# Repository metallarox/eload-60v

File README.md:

# eload-60v — 4-channel electronic load, 60 V · 20 A · 300 W

An open-hardware DC electronic load with four independent constant-current channels, 20-bit measurement on every channel, a hardware fail-safe that does not depend on firmware, and WiFi control through a plug-in ESP8266 module.

> **Status: rev 0.3 — design complete, not yet built or bench-tested.**
> ERC and DRC (with schematic parity) are clean, and the control loop and thermal budget have been analysed numerically. Treat it as a reviewed design, not a proven product. Bench reports, issues and pull requests are very welcome.

## Specifications

| Parameter | Value |
|---|---|
| Input voltage | 0 – 60 V (hardware OVP trips at 64.7 V) |
| Current | 4 channels × 0 – 5 A = 20 A |
| Power | 4 × 75 W = 300 W continuous (power-limited above 15 V) |
| Mode | Constant current per channel; CP / CR in firmware |
| Setpoint | DAC8565, 16 bit → 76 µA per LSB per channel |
| Measurement | INA228 per channel: 20-bit, Kelvin shunt, remote voltage sense |
| Control | WiFi, Wemos LOLIN D1 mini Pro (ESP8266) on sockets; front panel with I²C OLED, encoder and OUTPUT button |
| Protection | OVP, OTP, per-channel over-current/over-power ALERT, reverse-polarity crowbar, 25 A fuse |
| Loop | Phase margin ≈ 80°, closed-loop bandwidth 6 – 15 kHz (model) |
| PCB | 170 × 125 mm, 2 layers, 2 oz copper, KiCad 10 |

## How it works

- **Power path.** DUT+ → 25 A ATO fuse → VLOAD bus. A D²PAK Schottky (VS-30CTQ100S) acts as a reverse-polarity crowbar that blows the fuse, and an SMCJ64CA TVS clamps transients.
- **Channels.** Each channel is an OPA2196 integrator driving an IXYS **IXTH75N10L2** *Linear L2* MOSFET (extended FBSOA, designed for linear operation) with a 20 mΩ 4-terminal shunt (Vishay WSK2512). The setpoint is the DAC output divided by 25, referenced to the shunt's cold Kelvin pad: **I = V_DAC × 2 A/V**.
- **Measurement.** One INA228 per channel reads the shunt (Kelvin) and the remote-sense voltage. Its ALERT pin is wired to the common ARM line, so a programmed over-current or over-power limit shuts the load down in hardware.
- **Fail-safe.** ARM is active-high with a pull-down. It can be pulled low by the MCU, by the LM393 OVP/OTP comparators or by any INA228 ALERT. ARM low drives CLAMP high, which shorts all four setpoints to ground. No MCU, a reset or a boot glitch all leave the load off.
- **Thermal.** The four TO-247 parts are mounted *under* the PCB on an 80 × 70 × 6 mm copper spreader. The spreader sits at VLOAD (drain) potential, so it is isolated from an SP3/TR4-class CPU cooler by a thermal pad. Two NTC thermistors sit on the spreader.
- **Front panel (rev 0.3).** A 10-pin IDC connector carries the I²C bus to a 128 × 64 OLED (0x3C) and the encoder, its push switch, the OUTPUT button and its LED to a PCF8574 expander (0x20) on the main board. The expander's INT goes to GPIO0. The encoder works as a vernier: push toggles coarse/fine, long-press selects the channel. OUTPUT ON is the only way to arm the load from the panel.
- **Supplies.** An isolated 12 V adaptor feeds the op-amps and the fan. A 78L05 supplies the analog 5 V (DAC, comparators). A separate AP63205 buck feeds only the WiFi module, and its 3.3 V regulator powers the logic.

The full walkthrough, including SOA, thermal budget and loop-stability analysis, is in **[docs/Electronic_Load_Circuit_Walkthrough.pdf](docs/Electronic_Load_Circuit_Walkthrough.pdf)** (20 slides).

## Analysis highlights

| SOA | Loop gain |
|---|---|
|  |  |

- **SOA.** The worst steady point is 60 V × 1.25 A = 75 W per MOSFET. The guaranteed FBSOA (240 W at 80 V, T<sub>C</sub> 75 °C), derated to T<sub>C</sub> ≈ 96 °C, gives ≈ 173 W, a **2.3× margin**.
- **Thermal.** T<sub>J</sub> ≈ 119 °C at 35 °C ambient with a 0.12 K/W cooler. At the OTP trip point (spreader ~100 °C) T<sub>J</sub> ≈ 139 °C. To run 300 W continuously the cooler plus pad must be ≤ 0.22 K/W.
- **Loop.** Rev 0.1 used 10 nF compensation: stable, but only 0.6 – 1.5 kHz bandwidth and a turn-on delay of about 2 ms. **Rev 0.2 uses C6 = 1 nF and C5 = 10 nF:** PM ≈ 80°, 6 – 15 kHz, about 28 µs for small steps. A 10 mA keep-alive in firmware cuts the turn-on from the clamp to about 39 µs.

The model and scripts are in [`analysis/`](analysis/). Op-amp second pole and output resistance, the cooler's thermal resistance and the pad are **assumptions**, listed in the slides.

## Repository layout

```
hardware/
  kicad/          KiCad 10 project (eload_4ch.kicad_pro), custom symbols, DRC rules
  fabrication/    Gerbers + drill (zip) and pick-and-place positions, rev 0.3
  bom/            BOM from KiCad (CSV) and priced BOM with sources (XLSX)
docs/
  Electronic_Load_Circuit_Walkthrough.pdf   slide deck (English)
  assembly/       interactive HTML BOM, top/bottom assembly drawings
  eload_4ch_schematic.pdf, eload_4ch_pcb.pdf
  images/, reports/ (ERC / DRC)
firmware/         ESP8266 firmware (Arduino core), web page, unit tests, mock server, prebuilt bin
analysis/         loop model (sympy/scipy), large-signal sim, SOA/thermal plots
tools/generator/  Python scripts that generated the schematic and placed/routed the PCB
```

Schematic, PCB and the KiCad BOM are in English. The priced BOM workbook (`eload_4ch_bom_priced.xlsx`) and the code comments in `tools/` are still in Italian.

## Building one

1. **PCB.** Use `hardware/fabrication/eload_4ch_gerbers_rev0.3.zip`: 2 layers, 1.6 mm, **2 oz** copper. Many fabs require ≥ 0.2 mm spacing with 2 oz copper, while the INA228 MSOP-10 pads are 0.15 mm apart (the project has a local DRC exception for them). Confirm with your fab, or order 1 oz outer layers.
2. **Parts.** See `hardware/bom/eload_4ch_bom_priced.xlsx`. The electronics cost is about €126 per board at single quantities (October 2026). The four IXTH75N10L2 are about half of that and can have long factory lead times.
3. **Mechanics and front panel.** Copper spreader, insulating thermal pad (≥ 100 V), CPU cooler with a 4-wire PWM fan, M3 nylon standoffs, M5 bolts for the DUT studs. Front panel: 2.42″ SSD1309 or 1.3″ SH1106 I²C OLED, EC11 encoder with push, OUTPUT button with LED, 10-wire ribbon (≤ 20 cm). J6 pinout: 1 3V3 · 2 GND · 3 SDA · 4 GND · 5 SCL · 6 ENC_A · 7 ENC_B · 8 ENC_SW · 9 OUTPUT · 10 LED (cathode, 470 Ω on board).
4. **Assembly.** Open `docs/assembly/eload_4ch_ibom.html` in a browser: an interactive BOM that highlights where each part goes, with checkboxes to track sourced and placed parts. `docs/assembly/assembly_top.pdf` and `assembly_bottom.pdf` (the four MOSFETs) show every reference inside its part outline. The silkscreen has no overlaps: each reference designator is next to its component.
5. **Firmware.** See [firmware/README.md](firmware/README.md). A prebuilt image is in `firmware/bin/`. On first start the load opens a WiFi access point for setup; afterwards the page is at `http://eload.local`.

| Pin | GPIO | Function |
|---|---|---|
| D1 / D2 | 5 / 4 | I²C SCL / SDA → INA228 0x40 – 0x43, PCF8574 0x20, OLED 0x3C |
| D5 / D7 / D8 | 14 / 13 / 15 | SPI SCK / MOSI / SYNC → DAC8565 |
| D6 | 12 | ARM_DRV (quiet at boot) — re-assigned as output after `SPI.begin()` |
| D0 | 16 | ARM_FB read-back (100 k) |
| D3 | 0 | PCF8574 INT (front panel) |
| D4 | 2 | Fan PWM |
| RX | 3 | Fan tach |
| A0 | — | NTC1 |

## Firmware

v0.2.0 for the D1 mini Pro. It compiles and its control math is unit-tested, but it has **not yet run on hardware**.
- **Control:** CC / CP / CR with the setpoint shared by the channels, hardware and firmware protections with the trip cause reported, battery cutoff, auto-trim.
- **Pulsed load:** the sink switches between the setpoint and 10 mA at 0.1 Hz – 1 kHz with an adjustable duty, set from the panel menu or the web page.
- **Front panel:** OLED with the logo at boot, encoder used as a vernier and to drive the menu, OUTPUT button.
- **Logging:** CSV on the 14 MB flash.
- **Web:** live chart, controls, OTA update.

## ⚠️ Safety

- The whole controller, including the Wemos USB port, is referenced to **DUT−**. **USB is not isolated:** only program the module with the DUT disconnected, then update over the air. The 12 V adaptor must be isolated.
- The copper spreader and the MOSFET tabs are **live at the DUT voltage**.
- 300 W of heat is real. Do not run full power without the cooler and fan, and verify the OTP before trusting it.

## To verify on the bench

- Loop step response (1.0 ↔ 1.2 A) into a stiff supply, then with 1 m of DUT cable.
- D1 crowbar surviving the fuse I²t on reversed connection.
- Thermal resistance of the actual cooler and pad; OTP trip point.
- WiFi range with the antenna overhanging the board edge inside the enclosure.
- I²C signal integrity with the OLED on a 20 cm ribbon (2.2 kΩ pull-ups).

## Changelog

- **firmware 0.2.0** — pulsed load (frequency 0.1 Hz – 1 kHz, duty 1 – 99 %, phases ≥ 100 µs) in the panel menu, the web page, the API and the CSV.
- **firmware 0.1.0** — first firmware: control, protections, OLED + encoder panel, CSV logging, web interface, OTA.

- **rev 0.3** — front panel: PCF8574 expander, 10-pin IDC connector, debounce, I²C pull-ups 2.2 kΩ. Schematic and PCB translated to English (sheets: input, channels, control, power). Silkscreen cleaned up: no overlaps, references next to their parts; interactive BOM and assembly drawings.
- **rev 0.2** — loop compensation C6 = 1 nF, setpoint filter C5 = 10 nF (10× bandwidth, PM ≈ 80°); WiFi control with D1 mini Pro replaces STM32 + isolated USB.

## Credits

Inspired by [shufps/eload2](https://github.com/shufps/eload2). Designed by IV3HGA.

## License

- Hardware (everything under `hardware/` and `docs/`): **CERN-OHL-S-2.0** — see [LICENSE](LICENSE).
- Software (`firmware/`, `analysis/`, `tools/`): **MIT** — see [LICENSE-MIT](LICENSE-MIT).

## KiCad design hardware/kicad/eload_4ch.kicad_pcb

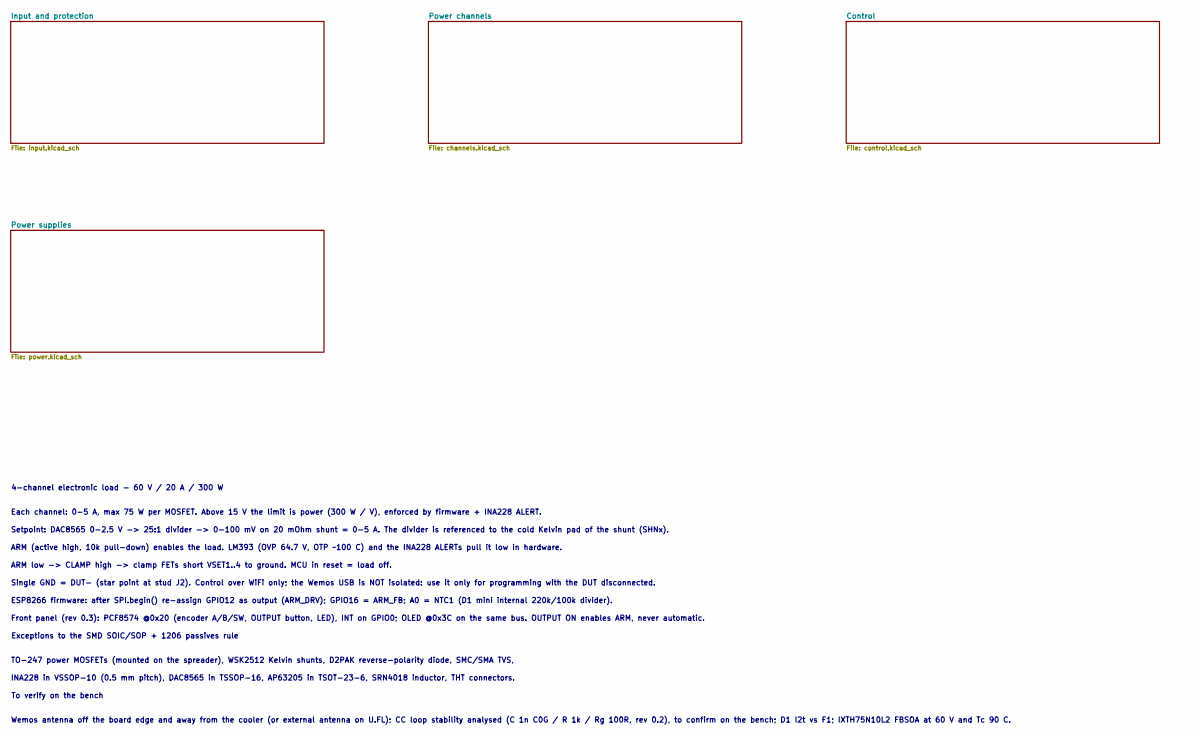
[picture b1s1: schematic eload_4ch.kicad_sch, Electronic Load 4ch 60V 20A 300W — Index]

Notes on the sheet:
Wemos antenna off the board edge and away from the cooler (or external antenna on U.FL); CC loop stability analysed (C 1n C0G / R 1k / Rg 100R, rev 0.2), to confirm on the bench; D1 I2t vs F1; IXTH75N10L2 FBSOA at 60 V and Tc 90 C.
INA228 in VSSOP-10 (0.5 mm pitch), DAC8565 in TSSOP-16, AP63205 in TSOT-23-6, SRN4018 inductor, THT connectors.
ARM low -> CLAMP high -> clamp FETs short VSET1..4 to ground. MCU in reset = load off.
Front panel (rev 0.3): PCF8574 @0x20 (encoder A/B/SW, OUTPUT button, LED), INT on GPIO0; OLED @0x3C on the same bus. OUTPUT ON enables ARM, never automatic.
Setpoint: DAC8565 0-2.5 V -> 25:1 divider -> 0-100 mV on 20 mOhm shunt = 0-5 A. The divider is referenced to the cold Kelvin pad of the shunt (SHNx).
4-channel electronic load - 60 V / 20 A / 300 W
To verify on the bench
ESP8266 firmware: after SPI.begin() re-assign GPIO12 as output (ARM_DRV); GPIO16 = ARM_FB; A0 = NTC1 (D1 mini internal 220k/100k divider).
Single GND = DUT- (star point at stud J2). Control over WiFi only; the Wemos USB is NOT isolated: use it only for programming with the DUT disconnected.
ARM (active high, 10k pull-down) enables the load. LM393 (OVP 64.7 V, OTP ~100 C) and the INA228 ALERTs pull it low in hardware.
Each channel: 0-5 A, max 75 W per MOSFET. Above 15 V the limit is power (300 W / V), enforced by firmware + INA228 ALERT.
Exceptions to the SMD SOIC/SOP + 1206 passives rule
TO-247 power MOSFETs (mounted on the spreader), WSK2512 Kelvin shunts, D2PAK reverse-polarity diode, SMC/SMA TVS,

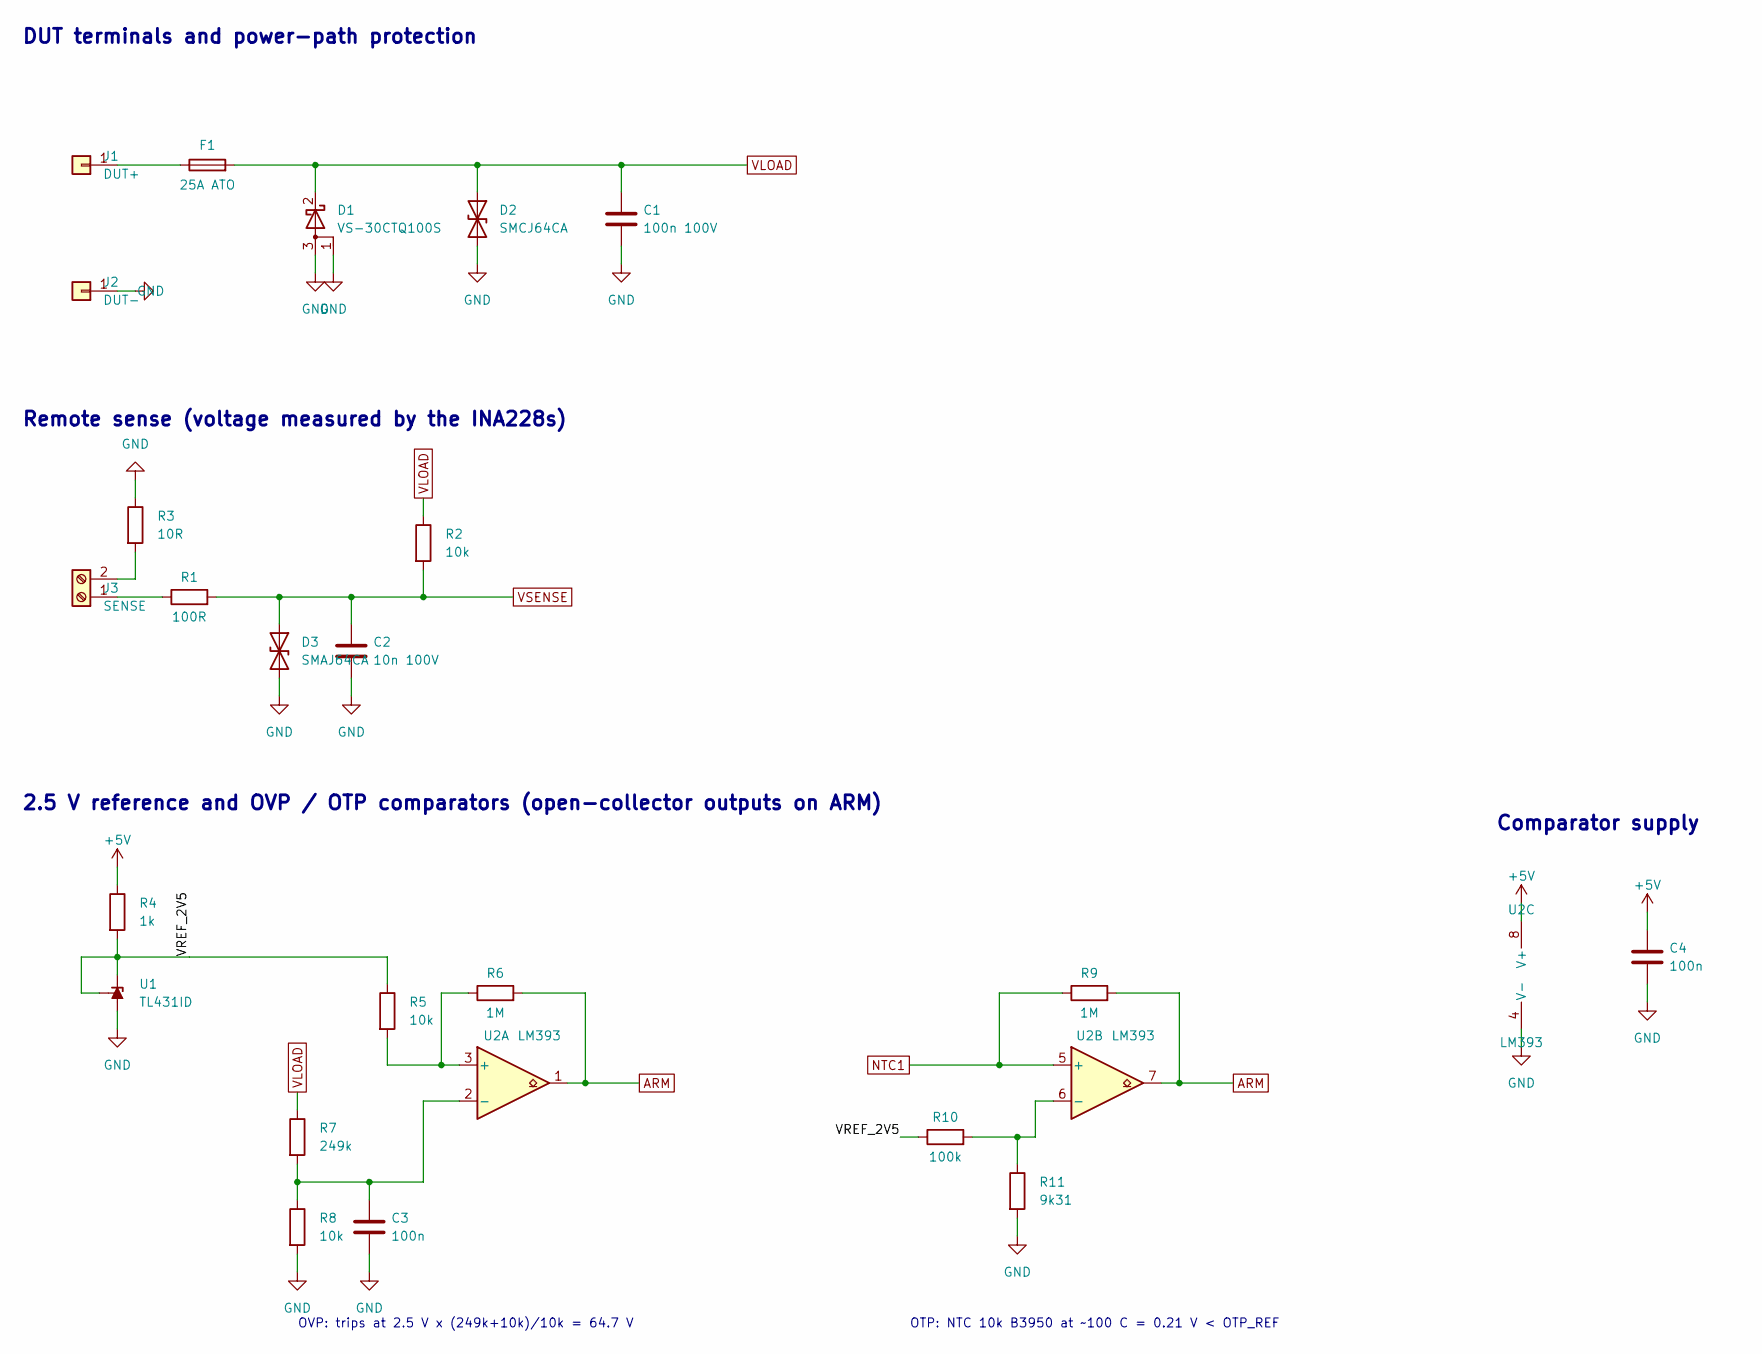
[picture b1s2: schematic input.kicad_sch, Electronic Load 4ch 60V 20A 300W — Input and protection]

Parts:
C1: 100n 100V; C_1206_3216Metric
C2: 10n 100V; C_1206_3216Metric
C3, C4: 100n; C_1206_3216Metric
D1: VS-30CTQ100S; TO-263-2; MPN VS-30CTQ100SPbF
D2: SMCJ64CA; D_SMC; MPN SMCJ64CA
D3: SMAJ64CA; D_SMA; MPN SMAJ64CA
F1: 25A ATO; Fuseholder_Blade_ATO_Littelfuse_Pudenz_2_Pin
J1: DUT+; MountingHole_5.3mm_M5_Pad_Via
J2: DUT-; MountingHole_5.3mm_M5_Pad_Via
J3: SENSE; TerminalBlock_Phoenix_MKDS-1,5-2_1x02_P5.00mm_Horizontal
R1: 100R; R_1206_3216Metric
R2, R5, R8: 10k; R_1206_3216Metric
R3: 10R; R_1206_3216Metric
R4: 1k; R_1206_3216Metric
R6, R9: 1M; R_1206_3216Metric
R7: 249k; R_1206_3216Metric
R10: 100k; R_1206_3216Metric
R11: 9k31; R_1206_3216Metric
U1: TL431ID; SOIC-8_3.9x4.9mm_P1.27mm; MPN TL431IDR
U2: LM393; SOIC-8_3.9x4.9mm_P1.27mm; MPN LM393DR

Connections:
+5V: C4.1, R4.1, U2.8 (V+); also elsewhere on the board
/Input and protection/VREF_2V5: R4.2, R5.1, R10.1, U1.1 (K), U1.8 (REF)
ARM: R6.2, R9.2, U2.1, U2.7; also elsewhere on the board
GND: C1.2, C2.2, C3.2, C4.2, D1.1 (A), D1.3 (A), D2.2 (A2), D3.2 (A2), J2.1, R3.1, R8.2, R11.2, U1.2, U1.3, U1.6, U1.7, U1.[2,3,6,7] (A), U2.4 (V-); also elsewhere on the board
NTC1: R9.1, U2.5 (+); also elsewhere on the board
unnamed: F1.1, J1.1
unnamed: J3.1, R1.1
unnamed: J3.2, R3.2
unnamed: R5.2, R6.1, U2.3 (+)
unnamed: C3.1, R7.2, R8.1, U2.2 (-)
unnamed: R10.2, R11.1, U2.6 (-)
VLOAD: C1.1, D1.2 (K), D2.1 (A1), F1.2, R2.1, R7.1; also elsewhere on the board
VSENSE: C2.1, D3.1 (A1), R1.2, R2.2; also elsewhere on the board

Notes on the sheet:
DUT terminals and power-path protection
Remote sense (voltage measured by the INA228s)
2.5 V reference and OVP / OTP comparators (open-collector outputs on ARM)
OVP: trips at 2.5 V x (249k+10k)/10k = 64.7 V
OTP: NTC 10k B3950 at ~100 C = 0.21 V < OTP_REF
Comparator supply

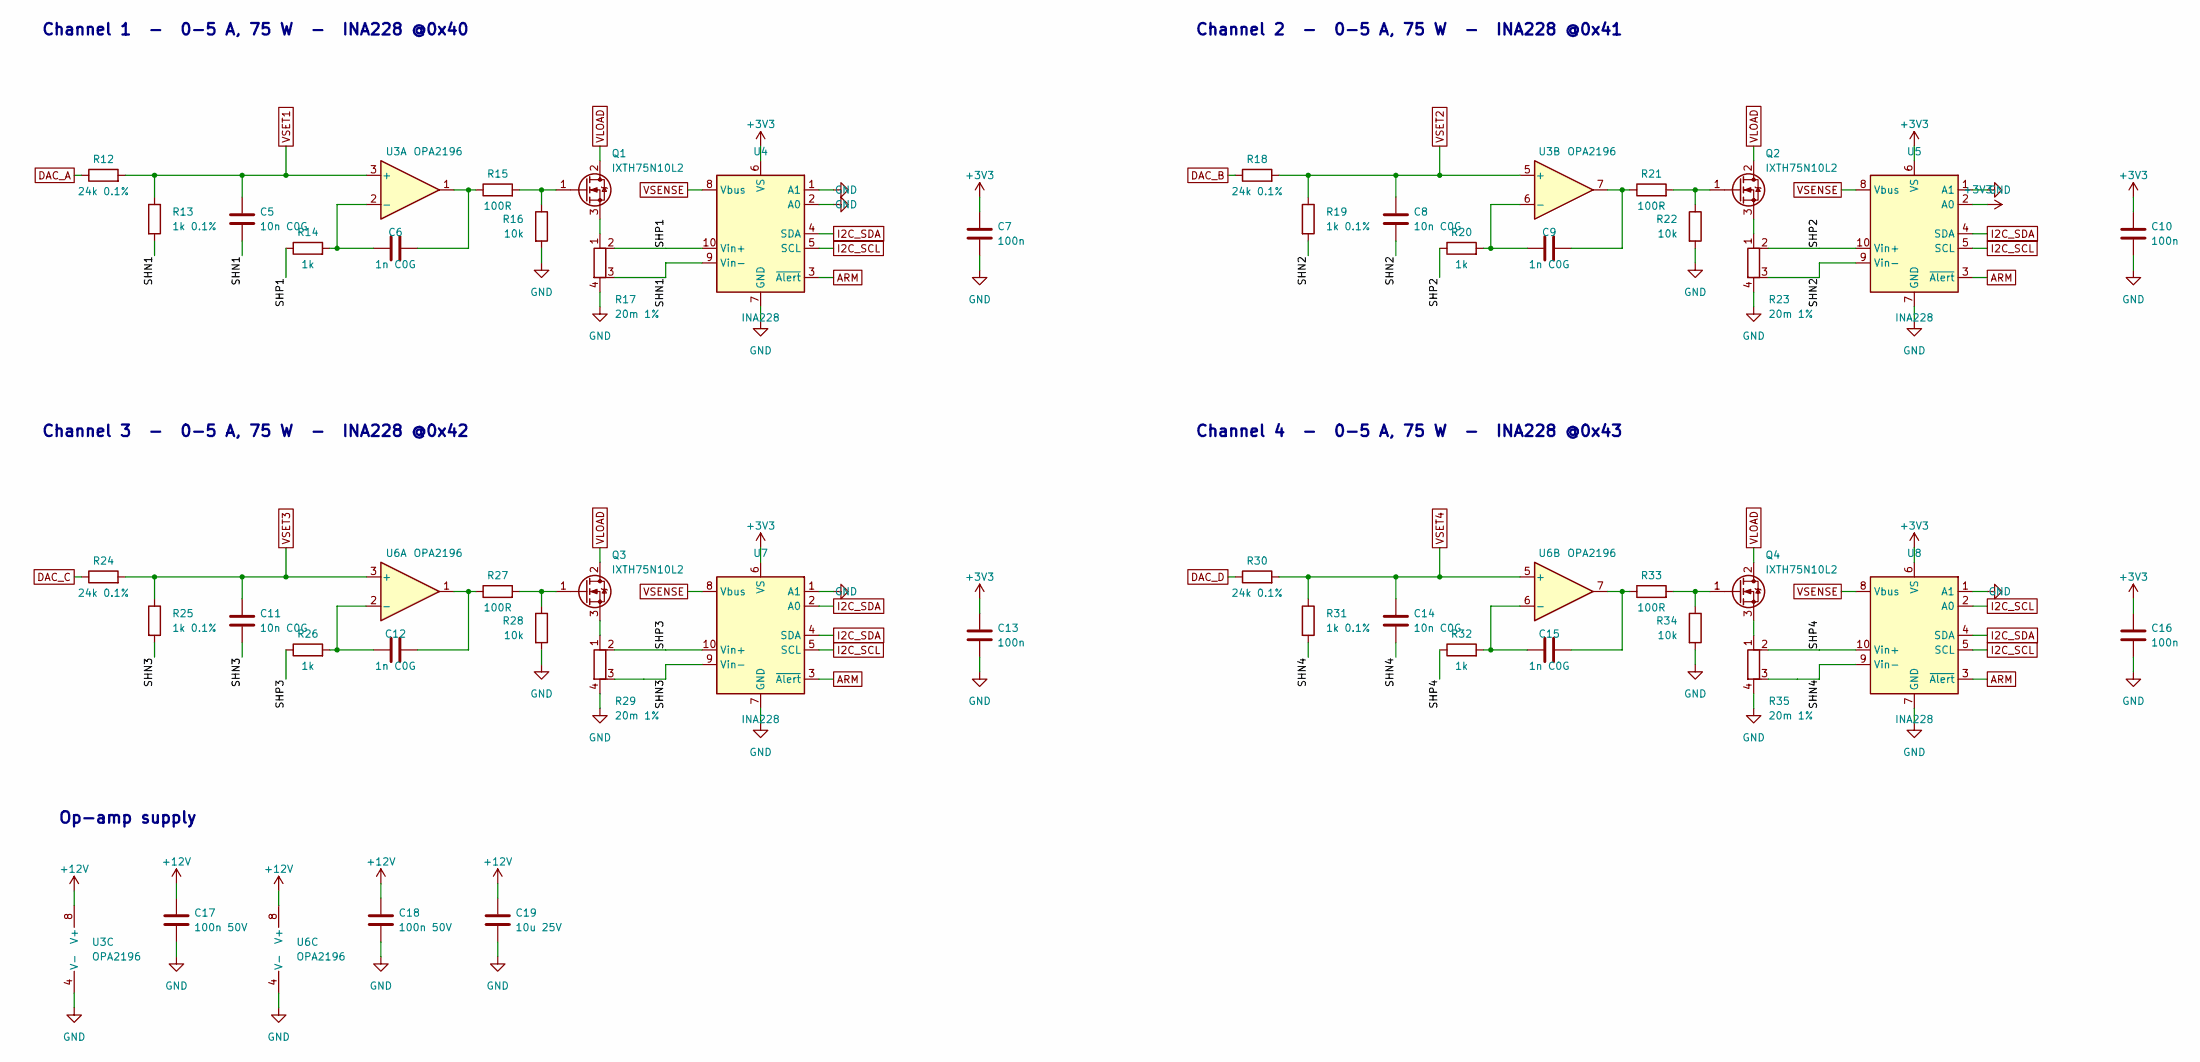
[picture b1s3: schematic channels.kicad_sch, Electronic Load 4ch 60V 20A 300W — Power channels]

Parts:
C5, C8, C11, C14: 10n C0G; C_1206_3216Metric
C6, C9, C12, C15: 1n C0G; C_1206_3216Metric
C7, C10, C13, C16: 100n; C_1206_3216Metric
C17, C18: 100n 50V; C_1206_3216Metric
C19: 10u 25V; C_1206_3216Metric
Q1, Q2, Q3, Q4: IXTH75N10L2; TO-247-3_Horizontal_TabUp; MPN IXTH75N10L2
R12, R18, R24, R30: 24k 0.1%; R_1206_3216Metric
R13, R19, R25, R31: 1k 0.1%; R_1206_3216Metric
R14, R20, R26, R32: 1k; R_1206_3216Metric
R15, R21, R27, R33: 100R; R_1206_3216Metric
R16, R22, R28, R34: 10k; R_1206_3216Metric
R17, R23, R29, R35: 20m 1%; R_Shunt_Vishay_WSK2512_6332Metric_T1.19mm; MPN WSK2512R0200FEA
U3, U6: OPA2196; SOIC-8_3.9x4.9mm_P1.27mm; MPN OPA2196IDR
U4, U5, U7, U8: INA228; MSOP-10_3x3mm_P0.5mm; MPN INA228AIDGSR

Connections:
+3V3: C7.1, C10.1, C13.1, C16.1, U4.6 (VS), U5.2 (A0), U5.6 (VS), U7.6 (VS), U8.6 (VS); also elsewhere on the board
+12V: C17.1, C18.1, C19.1, U3.8 (V+), U6.8 (V+); also elsewhere on the board
/Power channels/SHN1: C5.2, R13.2, R17.3, U4.9 (Vin-)
/Power channels/SHN2: C8.2, R19.2, R23.3, U5.9 (Vin-)
/Power channels/SHN3: C11.2, R25.2, R29.3, U7.9 (Vin-)
/Power channels/SHN4: C14.2, R31.2, R35.3, U8.9 (Vin-)
/Power channels/SHP1: R14.1, R17.2, U4.10 (Vin+)
/Power channels/SHP2: R20.1, R23.2, U5.10 (Vin+)
/Power channels/SHP3: R26.1, R29.2, U7.10 (Vin+)
/Power channels/SHP4: R32.1, R35.2, U8.10 (Vin+)
ARM: U4.3 (~Alert), U5.3 (~Alert), U7.3 (~Alert), U8.3 (~Alert); also elsewhere on the board
DAC_A: R12.1; also elsewhere on the board
DAC_B: R18.1; also elsewhere on the board
DAC_C: R24.1; also elsewhere on the board
DAC_D: R30.1; also elsewhere on the board
GND: C7.2, C10.2, C13.2, C16.2, C17.2, C18.2, C19.2, R16.2, R17.4, R22.2, R23.4, R28.2, R29.4, R34.2, R35.4, U3.4 (V-), U4.1 (A1), U4.2 (A0), U4.7 (GND), U5.1 (A1), U5.7 (GND), U6.4 (V-), U7.1 (A1), U7.7 (GND), U8.1 (A1), U8.7 (GND); also elsewhere on the board
I2C_SCL: U4.5 (SCL), U5.5 (SCL), U7.5 (SCL), U8.2 (A0), U8.5 (SCL); also elsewhere on the board
I2C_SDA: U4.4 (SDA), U5.4 (SDA), U7.2 (A0), U7.4 (SDA), U8.4 (SDA); also elsewhere on the board
unnamed: C6.2, R15.1, U3.1
unnamed: C9.2, R21.1, U3.7
unnamed: C12.2, R27.1, U6.1
unnamed: C15.2, R33.1, U6.7
unnamed: Q1.1 (G), R15.2, R16.1
unnamed: Q1.3 (S), R17.1
unnamed: Q2.1 (G), R21.2, R22.1
unnamed: Q2.3 (S), R23.1
unnamed: Q3.1 (G), R27.2, R28.1
unnamed: Q3.3 (S), R29.1
unnamed: Q4.1 (G), R33.2, R34.1
unnamed: Q4.3 (S), R35.1
unnamed: C6.1, R14.2, U3.2 (-)
unnamed: C9.1, R20.2, U3.6 (-)
unnamed: C12.1, R26.2, U6.2 (-)
unnamed: C15.1, R32.2, U6.6 (-)
VLOAD: Q1.2 (D), Q2.2 (D), Q3.2 (D), Q4.2 (D); also elsewhere on the board
VSENSE: U4.8 (Vbus), U5.8 (Vbus), U7.8 (Vbus), U8.8 (Vbus); also elsewhere on the board
VSET1: C5.1, R12.2, R13.1, U3.3 (+); also elsewhere on the board
VSET2: C8.1, R18.2, R19.1, U3.5 (+); also elsewhere on the board
VSET3: C11.1, R24.2, R25.1, U6.3 (+); also elsewhere on the board
VSET4: C14.1, R30.2, R31.1, U6.5 (+); also elsewhere on the board

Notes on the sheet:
Channel 1 - 0-5 A, 75 W - INA228 @0x40
Channel 2 - 0-5 A, 75 W - INA228 @0x41
Channel 3 - 0-5 A, 75 W - INA228 @0x42
Channel 4 - 0-5 A, 75 W - INA228 @0x43
Op-amp supply

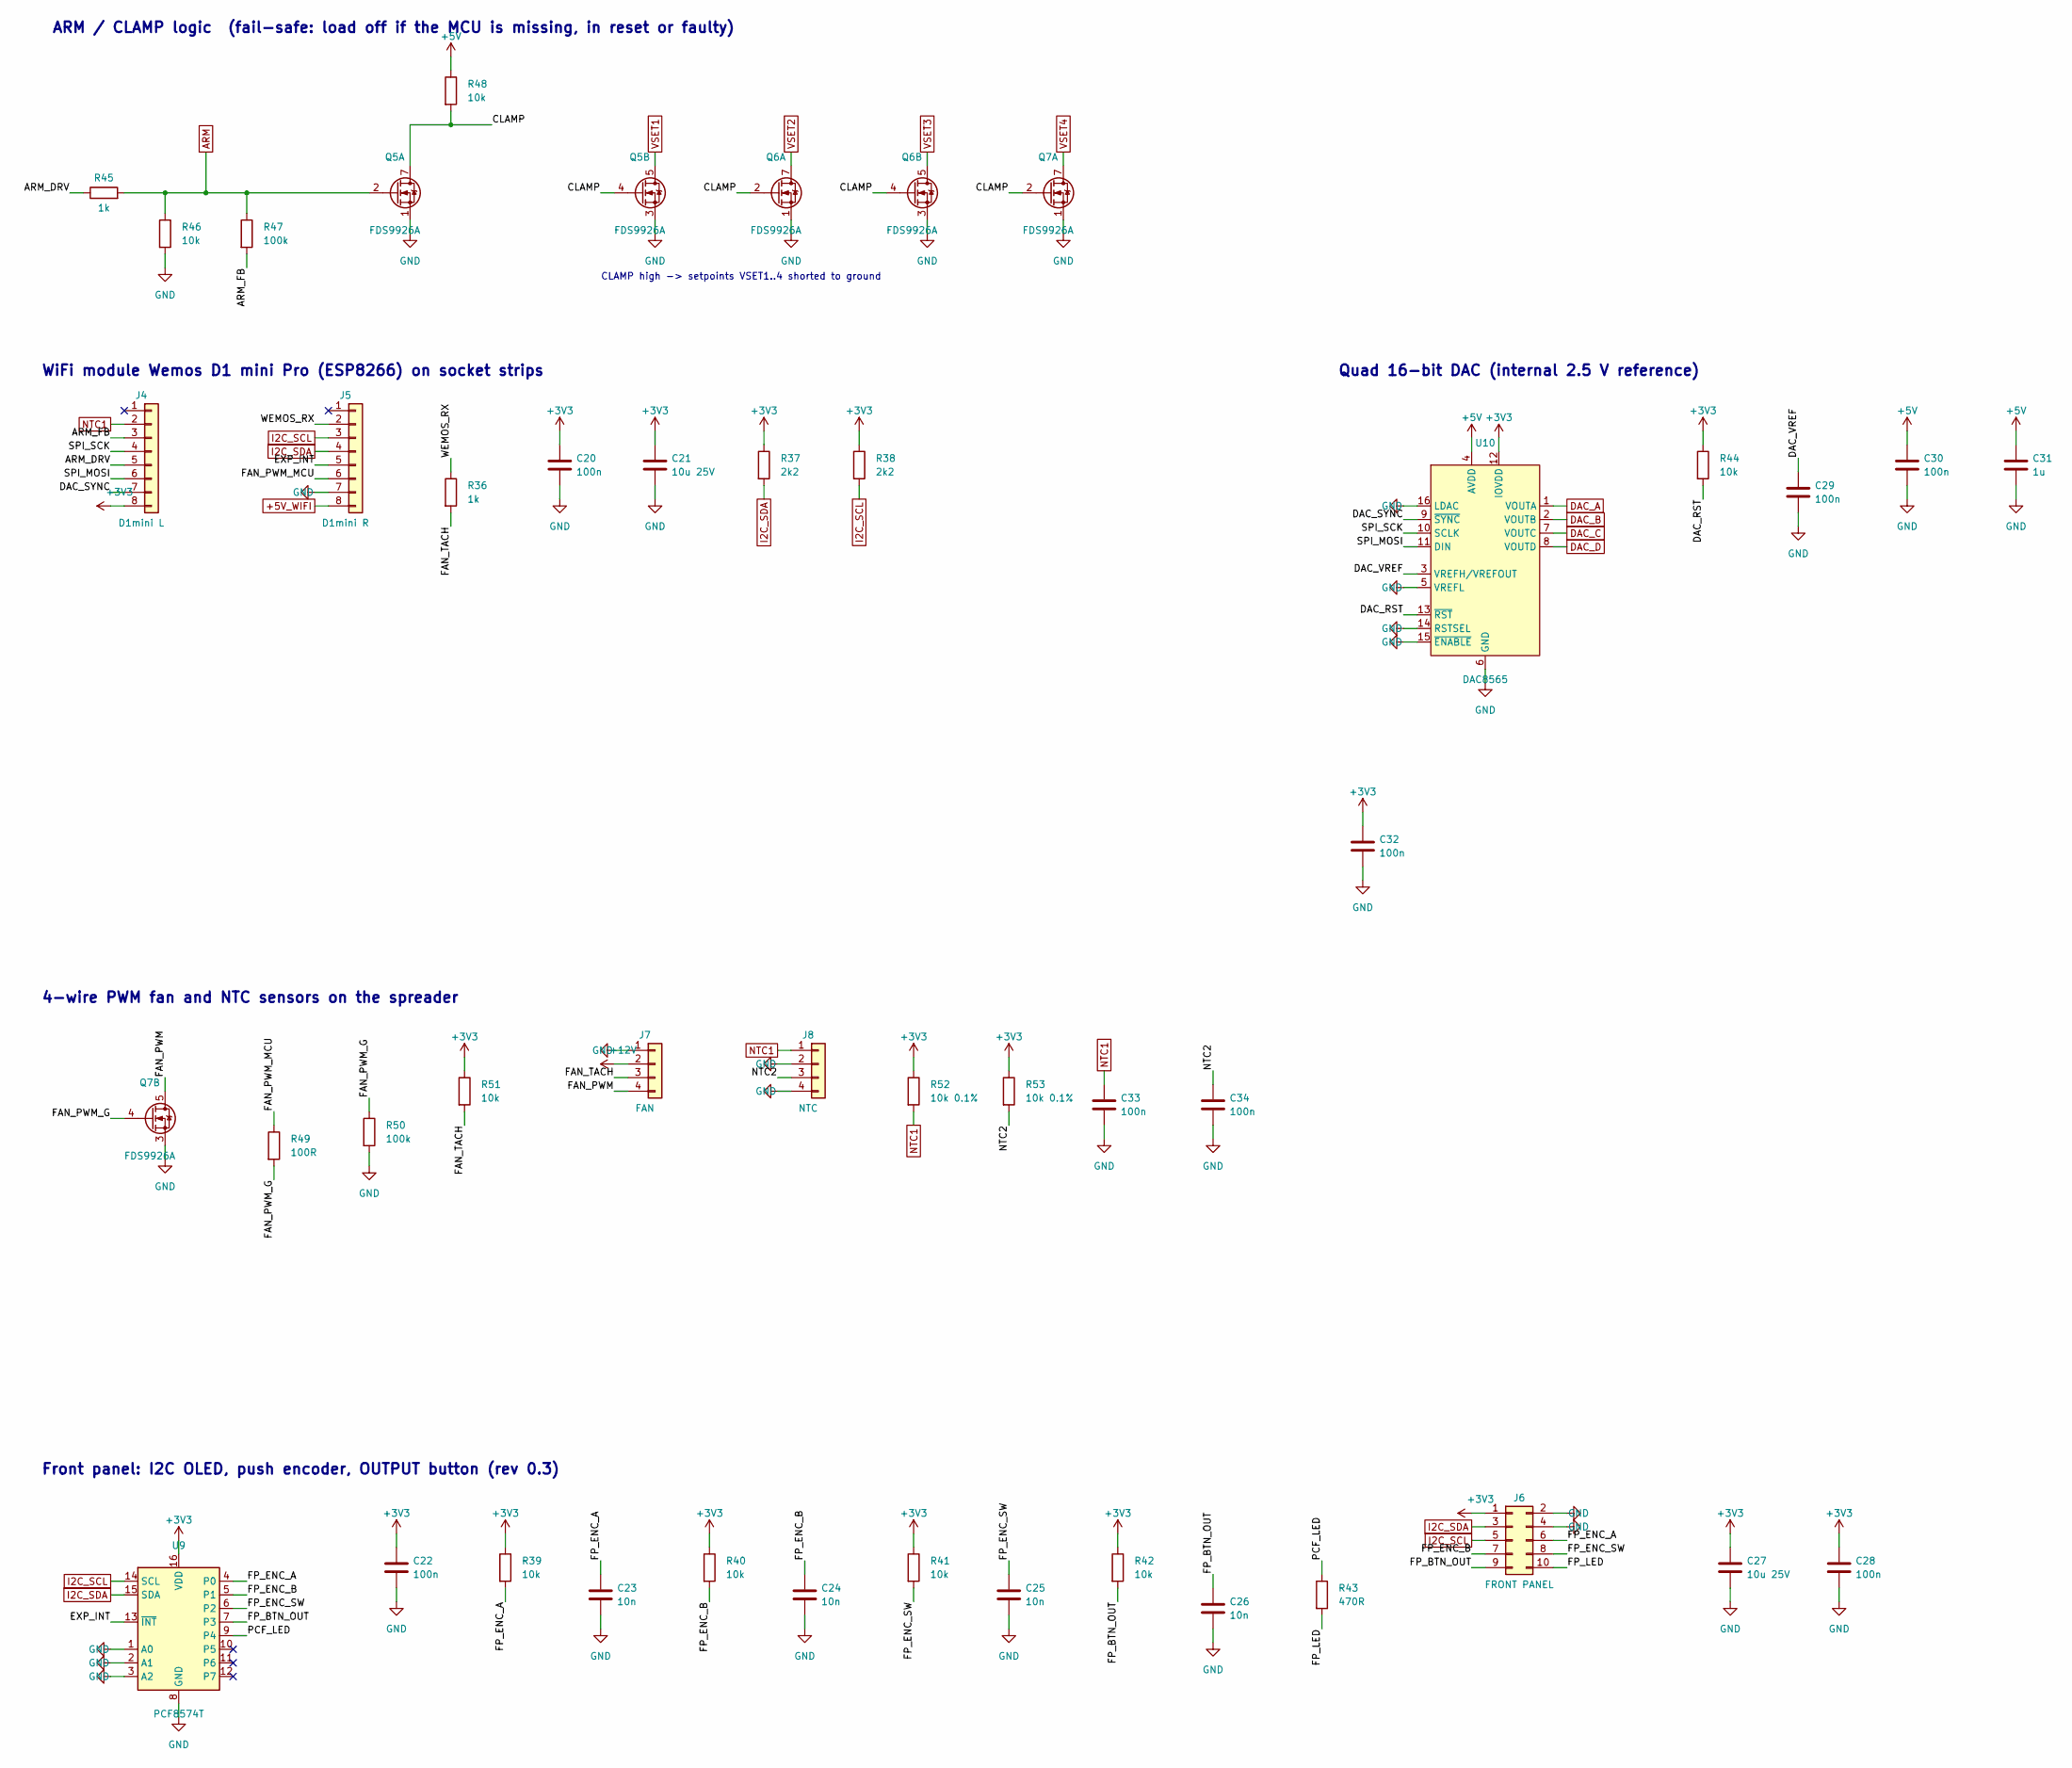
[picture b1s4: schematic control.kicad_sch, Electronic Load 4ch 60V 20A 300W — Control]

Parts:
C20, C22, C28, C29, C30, C32, C33, C34: 100n; C_1206_3216Metric
C21, C27: 10u 25V; C_1206_3216Metric
C23, C24, C25, C26: 10n; C_1206_3216Metric
C31: 1u; C_1206_3216Metric
J4: D1mini L; PinSocket_1x08_P2.54mm_Vertical
J5: D1mini R; PinSocket_1x08_P2.54mm_Vertical
J6: FRONT PANEL; IDC-Header_2x05_P2.54mm_Vertical
J7: FAN; Molex_KK-254_AE-6410-04A_1x04_P2.54mm_Vertical
J8: NTC; Molex_KK-254_AE-6410-04A_1x04_P2.54mm_Vertical
Q5, Q6, Q7: FDS9926A; SOIC-8_3.9x4.9mm_P1.27mm; MPN FDS9926A
R36, R45: 1k; R_1206_3216Metric
R37, R38: 2k2; R_1206_3216Metric
R39, R40, R41, R42, R44, R46, R48, R51: 10k; R_1206_3216Metric
R43: 470R; R_1206_3216Metric
R47, R50: 100k; R_1206_3216Metric
R49: 100R; R_1206_3216Metric
R52, R53: 10k 0.1%; R_1206_3216Metric
U9: PCF8574T; SOIC-16W_7.5x10.3mm_P1.27mm; MPN PCF8574T/3
U10: DAC8565; TSSOP-16_4.4x5mm_P0.65mm; MPN DAC8565IAPW

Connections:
+3V3: C20.1, C21.1, C22.1, C27.1, C28.1, C32.1, J4.8, J6.1, R37.1, R38.1, R39.1, R40.1, R41.1, R42.1, R44.1, R51.1, R52.1, R53.1, U9.16 (VDD), U10.12 (IOVDD); also elsewhere on the board
+5V: C30.1, C31.1, R48.1, U10.4 (AVDD); also elsewhere on the board
+5V_WIFI: J5.8; also elsewhere on the board
+12V: J7.2; also elsewhere on the board
/Control/ARM_DRV: J4.5, R45.1
/Control/ARM_FB: J4.3, R47.2
/Control/CLAMP: Q5.4 (G2), Q5.7 (D1), Q5.8 (D1), Q6.2 (G1), Q6.4 (G2), Q7.2 (G1), R48.2
/Control/DAC_RST: R44.2, U10.13 (~RST)
/Control/DAC_SYNC: J4.7, U10.9 (~SYNC)
/Control/DAC_VREF: C29.1, U10.3 (VREFH/VREFOUT)
/Control/EXP_INT: J5.5, U9.13 (~INT)
/Control/FAN_PWM: J7.4, Q7.5 (D2), Q7.6 (D2)
/Control/FAN_PWM_G: Q7.4 (G2), R49.2, R50.1
/Control/FAN_PWM_MCU: J5.6, R49.1
/Control/FAN_TACH: J7.3, R36.2, R51.2
/Control/FP_BTN_OUT: C26.1, J6.9, R42.2, U9.7 (P3)
/Control/FP_ENC_A: C23.1, J6.6, R39.2, U9.4 (P0)
/Control/FP_ENC_B: C24.1, J6.7, R40.2, U9.5 (P1)
/Control/FP_ENC_SW: C25.1, J6.8, R41.2, U9.6 (P2)
/Control/FP_LED: J6.10, R43.2
/Control/NTC2: C34.1, J8.3, R53.2
/Control/PCF_LED: R43.1, U9.9 (P4)
/Control/SPI_MOSI: J4.6, U10.11 (DIN)
/Control/SPI_SCK: J4.4, U10.10 (SCLK)
/Control/WEMOS_RX: J5.2, R36.1
ARM: Q5.2 (G1), R45.2, R46.1, R47.1; also elsewhere on the board
DAC_A: U10.1 (VOUTA); also elsewhere on the board
DAC_B: U10.2 (VOUTB); also elsewhere on the board
DAC_C: U10.7 (VOUTC); also elsewhere on the board
DAC_D: U10.8 (VOUTD); also elsewhere on the board
GND: C20.2, C21.2, C22.2, C23.2, C24.2, C25.2, C26.2, C27.2, C28.2, C29.2, C30.2, C31.2, C32.2, C33.2, C34.2, J5.7, J6.2, J6.4, J7.1, J8.2, J8.4, Q5.1 (S1), Q5.3 (S2), Q6.1 (S1), Q6.3 (S2), Q7.1 (S1), Q7.3 (S2), R46.2, R50.2, U9.1 (A0), U9.2 (A1), U9.3 (A2), U9.8 (GND), U10.5 (VREFL), U10.6 (GND), U10.14 (RSTSEL), U10.15 (~ENABLE), U10.16 (LDAC); also elsewhere on the board
I2C_SCL: J5.3, J6.5, R38.2, U9.14 (SCL); also elsewhere on the board
I2C_SDA: J5.4, J6.3, R37.2, U9.15 (SDA); also elsewhere on the board
NTC1: C33.1, J4.2, J8.1, R52.2; also elsewhere on the board
VSET1: Q5.5 (D2), Q5.6 (D2); also elsewhere on the board
VSET2: Q6.7 (D1), Q6.8 (D1); also elsewhere on the board
VSET3: Q6.5 (D2), Q6.6 (D2); also elsewhere on the board
VSET4: Q7.7 (D1), Q7.8 (D1); also elsewhere on the board

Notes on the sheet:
ARM / CLAMP logic (fail-safe: load off if the MCU is missing, in reset or faulty)
CLAMP high -> setpoints VSET1..4 shorted to ground
WiFi module Wemos D1 mini Pro (ESP8266) on socket strips
Front panel: I2C OLED, push encoder, OUTPUT button (rev 0.3)
Quad 16-bit DAC (internal 2.5 V reference)
4-wire PWM fan and NTC sensors on the spreader

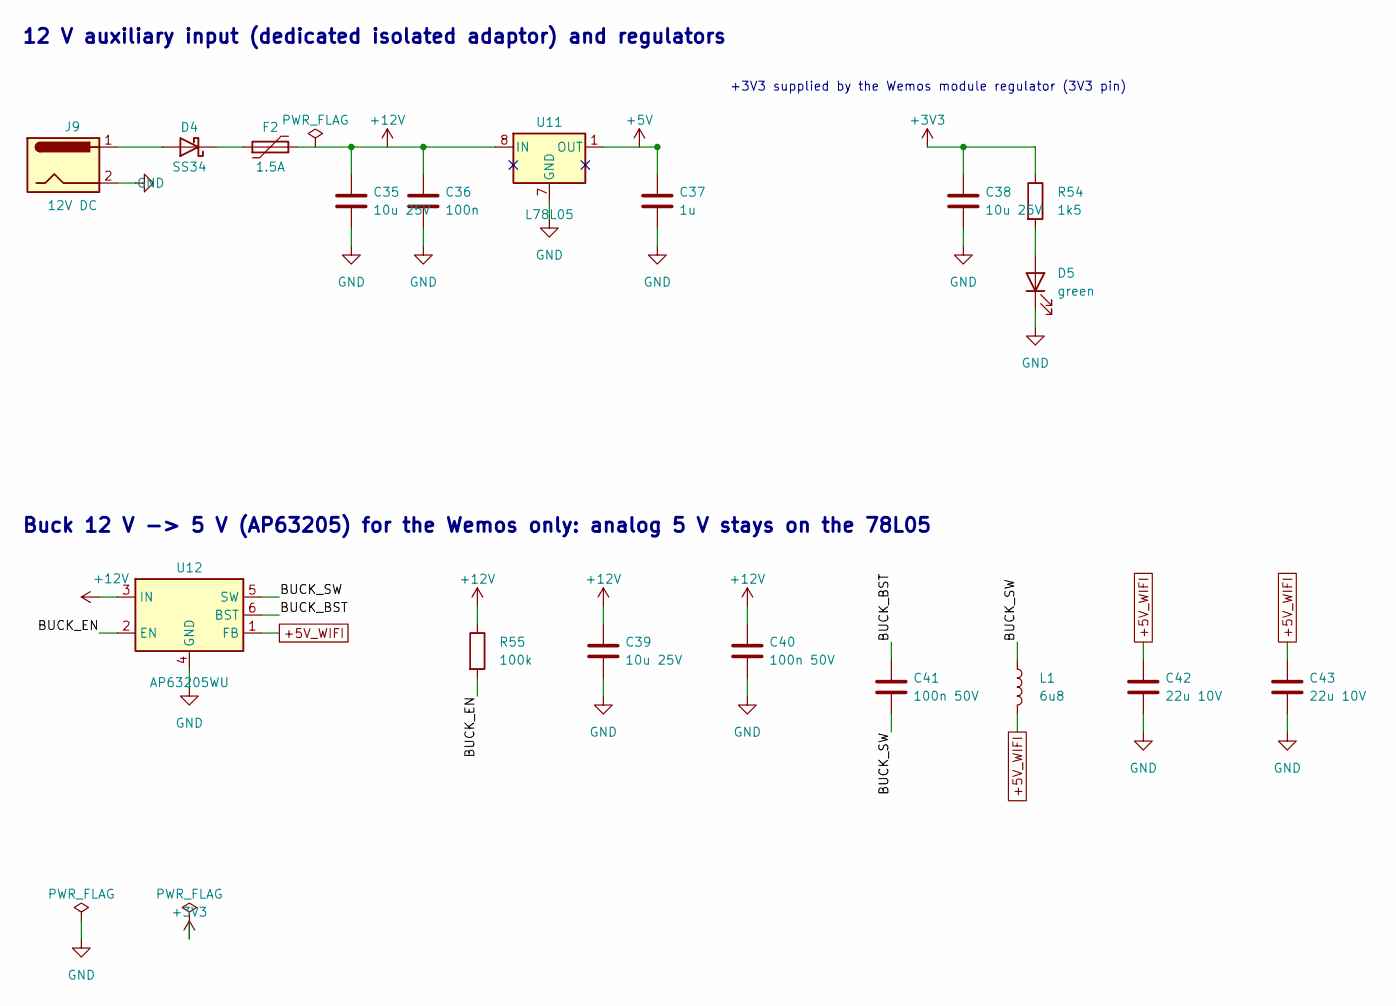
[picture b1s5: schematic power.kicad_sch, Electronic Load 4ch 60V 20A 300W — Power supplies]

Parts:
C35, C38, C39: 10u 25V; C_1206_3216Metric
C36: 100n; C_1206_3216Metric
C37: 1u; C_1206_3216Metric
C40, C41: 100n 50V; C_1206_3216Metric
C42, C43: 22u 10V; C_1206_3216Metric
D4: SS34; D_SMA; MPN SS34
D5: green; LED_1206_3216Metric
F2: 1.5A; Fuse_1206_3216Metric
J9: 12V DC; BarrelJack_Horizontal
L1: 6u8; L_Bourns-SRN4018; MPN SRN4018-6R8M
R54: 1k5; R_1206_3216Metric
R55: 100k; R_1206_3216Metric
U11: L78L05; SOIC-8_3.9x4.9mm_P1.27mm; MPN L78L05ACD13TR
U12: AP63205WU; TSOT-23-6; MPN AP63205WU-7

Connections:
+3V3: C38.1, R54.1; also elsewhere on the board
+5V: C37.1, U11.1 (OUT); also elsewhere on the board
+5V_WIFI: C42.1, C43.1, L1.2, U12.1 (FB); also elsewhere on the board
+12V: C35.1, C36.1, C39.1, C40.1, F2.2, R55.1, U11.8 (IN), U12.3 (IN); also elsewhere on the board
/Power supplies/BUCK_BST: C41.1, U12.6 (BST)
/Power supplies/BUCK_EN: R55.2, U12.2 (EN)
/Power supplies/BUCK_SW: C41.2, L1.1, U12.5 (SW)
GND: C35.2, C36.2, C37.2, C38.2, C39.2, C40.2, C42.2, C43.2, D5.1 (K), J9.2, U11.2 (GND), U11.3 (GND), U11.6 (GND), U11.7 (GND), U12.4 (GND); also elsewhere on the board
unnamed: D4.2 (A), J9.1
unnamed: D4.1 (K), F2.1
unnamed: D5.2 (A), R54.2

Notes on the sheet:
12 V auxiliary input (dedicated isolated adaptor) and regulators
+3V3 supplied by the Wemos module regulator (3V3 pin)
Buck 12 V -> 5 V (AP63205) for the Wemos only: analog 5 V stays on the 78L05
